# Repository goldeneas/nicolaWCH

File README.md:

# nicolaWCH
The smartwatch features:  
\- ESP32-S3-MINI-1  
\- USB TypeB Micro Connector + MIC5219-3.3YM5  
\- LSM6DS3  
\- I2C Display Module

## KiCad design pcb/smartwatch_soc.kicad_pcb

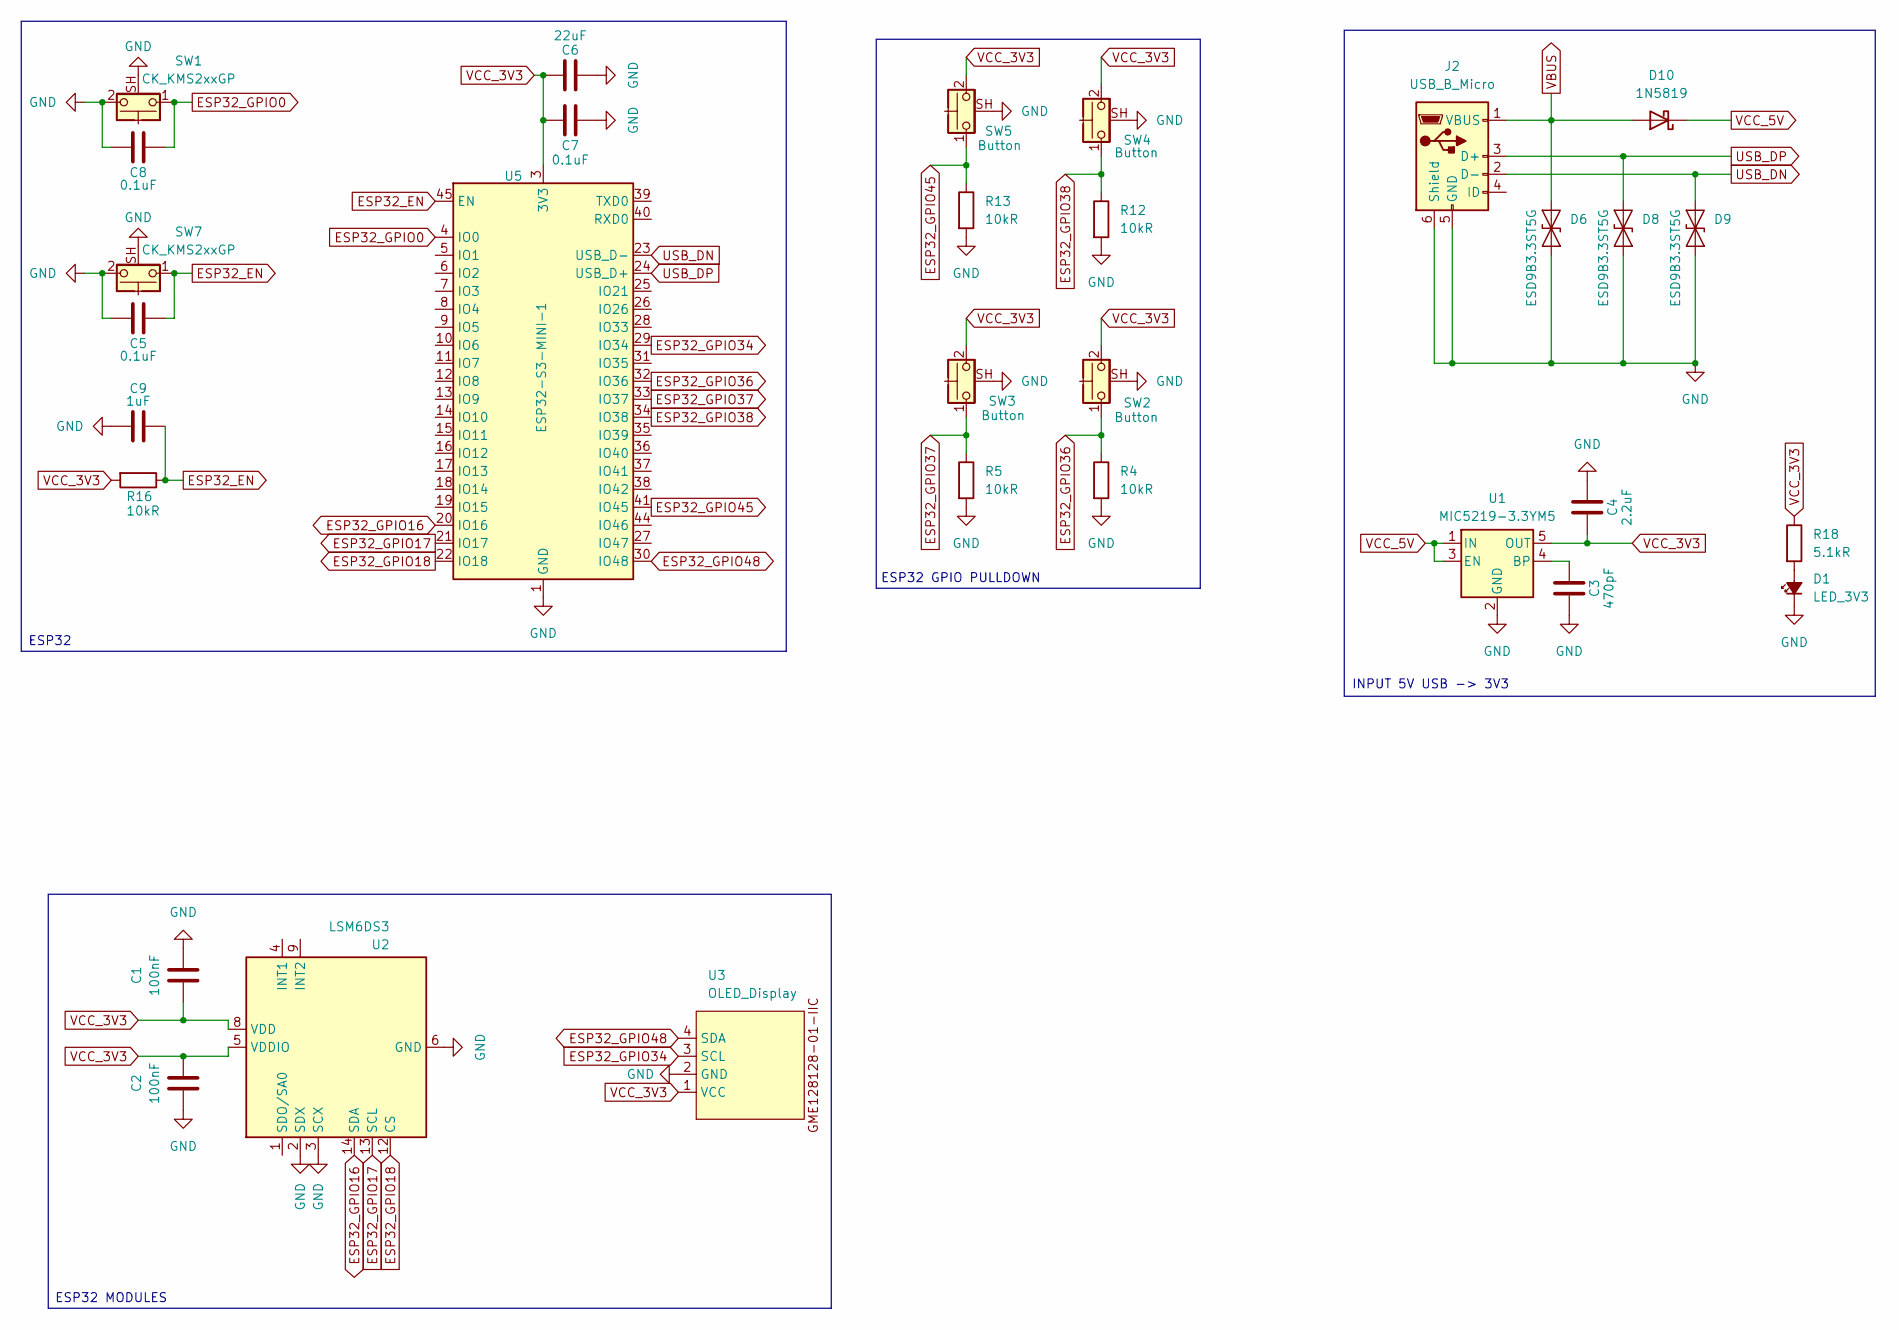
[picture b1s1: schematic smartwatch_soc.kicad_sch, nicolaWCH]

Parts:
C1, C2: 100nF; C_Disc_D5.0mm_W2.5mm_P2.50mm
C3: 470pF; C_Disc_D5.0mm_W2.5mm_P2.50mm
C4: 2.2uF; C_Disc_D5.0mm_W2.5mm_P2.50mm
C5, C7, C8: 0.1uF; C_Disc_D5.0mm_W2.5mm_P2.50mm
C6: 22uF; C_Disc_D5.0mm_W2.5mm_P2.50mm
C9: 1uF; C_Disc_D5.0mm_W2.5mm_P2.50mm
D1: LED_3V3; LED_D1.8mm_W3.3mm_H2.4mm
D6, D8, D9: ESD9B3.3ST5G; D_SOD-923
D10: 1N5819; D_DO-41_SOD81_P10.16mm_Horizontal
J2: USB_B_Micro; USB_Micro-B_Amphenol_10118194-0001LF_Horizontal
R4, R5, R12, R13, R16: 10kR; R_Axial_DIN0204_L3.6mm_D1.6mm_P5.08mm_Horizontal
R18: 5.1kR; R_Axial_DIN0204_L3.6mm_D1.6mm_P5.08mm_Horizontal
SW1, SW7: CK_KMS2xxGP; SW_SPST_CK_KMS2xxGP
SW2, SW3, SW4, SW5: Button; SW_SPST_CK_KMS2xxGP
U1: MIC5219-3.3YM5; SOT-23-5
U2: LSM6DS3; LGA-14_3x2.5mm_P0.5mm_LayoutBorder3x4y
U3: OLED_Display; PinHeader_1x04_P1.00mm_Vertical
U5: ESP32-S3-MINI-1; ESP32-S2-MINI-1

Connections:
ESP32_EN: C5.2, C9.2, R16.1, SW7.1, U5.45 (EN)
ESP32_GPIO0: C8.2, SW1.1, U5.4 (IO0)
ESP32_GPIO16: U2.14 (SDA), U5.20 (IO16)
ESP32_GPIO17: U2.13 (SCL), U5.21 (IO17)
ESP32_GPIO18: U2.12 (CS), U5.22 (IO18)
ESP32_GPIO34: U3.3 (SCL), U5.29 (IO34)
ESP32_GPIO36: R4.1, SW2.1, U5.32 (IO36)
ESP32_GPIO37: R5.1, SW3.1, U5.33 (IO37)
ESP32_GPIO38: R12.1, SW4.1, U5.34 (IO38)
ESP32_GPIO45: R13.1, SW5.1, U5.41 (IO45)
ESP32_GPIO48: U3.4 (SDA), U5.30 (IO48)
GND: C1.2, C2.1, C3.1, C4.2, C5.1, C6.1, C7.2, C8.1, C9.1, D1.1 (K), D6.1 (A1), D8.1 (A1), D9.1 (A1), J2.5 (GND), J2.6 (Shield), R4.2, R5.2, R12.2, R13.2, SW1.2, SW1.SH (B), SW2.SH (B), SW3.SH (B), SW4.SH (B), SW5.SH (B), SW7.2, SW7.SH (B), U1.2 (GND), U2.2 (SDX), U2.3 (SCX), U2.6 (GND), U2.7 (GND), U3.2 (GND), U5.1 (GND), U5.2 (GND), U5.42 (GND), U5.43 (GND), U5.46 (GND), U5.47 (GND), U5.48 (GND), U5.49 (GND), U5.50 (GND), U5.51 (GND), U5.52 (GND), U5.53 (GND), U5.54 (GND), U5.55 (GND), U5.56 (GND), U5.57 (GND), U5.58 (GND), U5.59 (GND), U5.60 (GND), U5.61 (GND), U5.62 (GND), U5.63 (GND), U5.64 (GND), U5.65 (GND)
unnamed: D1.2 (A), R18.2
unnamed: C3.2, U1.4 (BP)
USB_DN: D9.2 (A2), J2.2 (D-), U5.23 (USB_D-)
USB_DP: D8.2 (A2), J2.3 (D+), U5.24 (USB_D+)
VBUS: D6.2 (A2), D10.2 (A), J2.1 (VBUS)
VCC_3V3: C1.1, C2.2, C4.1, C6.2, C7.1, R16.2, R18.1, SW2.2, SW3.2, SW4.2, SW5.2, U1.5 (OUT), U2.5 (VDDIO), U2.8 (VDD), U3.1 (VCC), U5.3 (3V3)
VCC_5V: D10.1 (K), U1.1 (IN), U1.3 (EN)

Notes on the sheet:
ESP32 GPIO PULLDOWN
INPUT 5V USB -> 3V3
ESP32 MODULES
ESP32

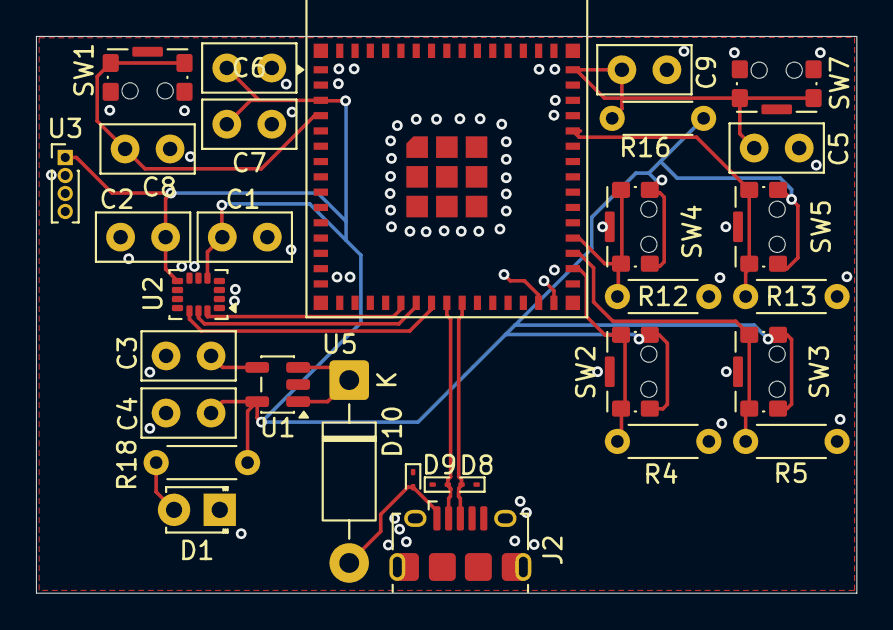
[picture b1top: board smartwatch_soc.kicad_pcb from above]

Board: 4 copper layers, 45.6 x 30.9 mm, 31 parts (0 on the bottom side), 19 nets.

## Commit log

2025-10-24 initialize README
2025-10-24 update README with image and formatting changes
2025-10-24 fix typo in README.md regarding picture description
2025-10-24 added images + put all code in src/
2025-10-25 fixed image drawn mirrored
2025-10-25 added button debouncing on release
2025-10-25 added input system
2025-10-26 input is now handled by input_system
2025-10-27 added pcb design
2025-10-27 use tht instead of smd for resistors, capacitors
2025-10-27 reset pcb designs
2025-10-27 added decoupling capacitors for accelerometer
2025-10-27 added capacitors for en/3.3V for ESP32
2025-10-28 bigger schematic page
2025-10-28 switched usba to micro usb type b
2025-10-28 referenced esp32-mini devkit
2025-10-28 fixed resistors for leds and capacitors for accelerometer
2025-10-28 use esp32-mini for antenna
2025-10-28 added footprints
2025-10-28 given tags in/out/bidirectional properties
2025-10-28 added shield pins for switches, better buttons for EN and GPIO0
2025-10-28 minor movement
2025-10-29 updated en and gpio0 circuits
2025-10-29 started pcb layout
2025-10-29 pcb design
2025-10-30 pcb design rules
2025-10-30 pcb design rules progress
2025-10-30 no more design errors!
2025-11-04 added labels
2025-11-06 updated image and readme
